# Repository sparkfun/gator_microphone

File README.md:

SparkFun gator:microphone - micro:bit Accessory Board 
=============================

[*SparkFun gator:microphone - micro:bit Accessory Board (SEN-15289)*](https://www.sparkfun.com/products/15289)  

(Modify Description)
Electret microphone with multiple outputs.

* First output is the actual audio
* Second output is the amplitude envelope
* Third output is a binary "sound present" indication - high while sound is present, low otherwise.

Design and firmware files for the [VKey Voltage Keypad](https://www.sparkfun.com/products/12080).

Repository Contents
-------------------

* **/Hardware** - Eagle design files (.brd, .sch)
* **/Production** - Production panel files (.brd)

Documentation
--------------

* **[Hookup Guide](https://learn.sparkfun.com/tutorials/sparkfun-gatormicrophone-hookup-guide)** - Basic hookup guide for the gator:microphone.
* **[gator:microphone PXT Package](https://github.com/sparkfun/pxt-gator-microphone)** - PXT- package for the MakeCode gator:microphone extension.

License Information
-------------------

This product is _**open source**_! 

Please review the LICENSE.md file for license information. 

If you have any questions or concerns on licensing, please visit the [SparkFun Forum](https://forum.sparkfun.com/index.php) and post a topic. For more general questions related to our gator boards, please visit this section of the forum: [SparkFun Forums: Educational Products](https://forum.sparkfun.com/viewforum.php?f=155)

Distributed as-is; no warranty is given.

- Your friends at SparkFun.

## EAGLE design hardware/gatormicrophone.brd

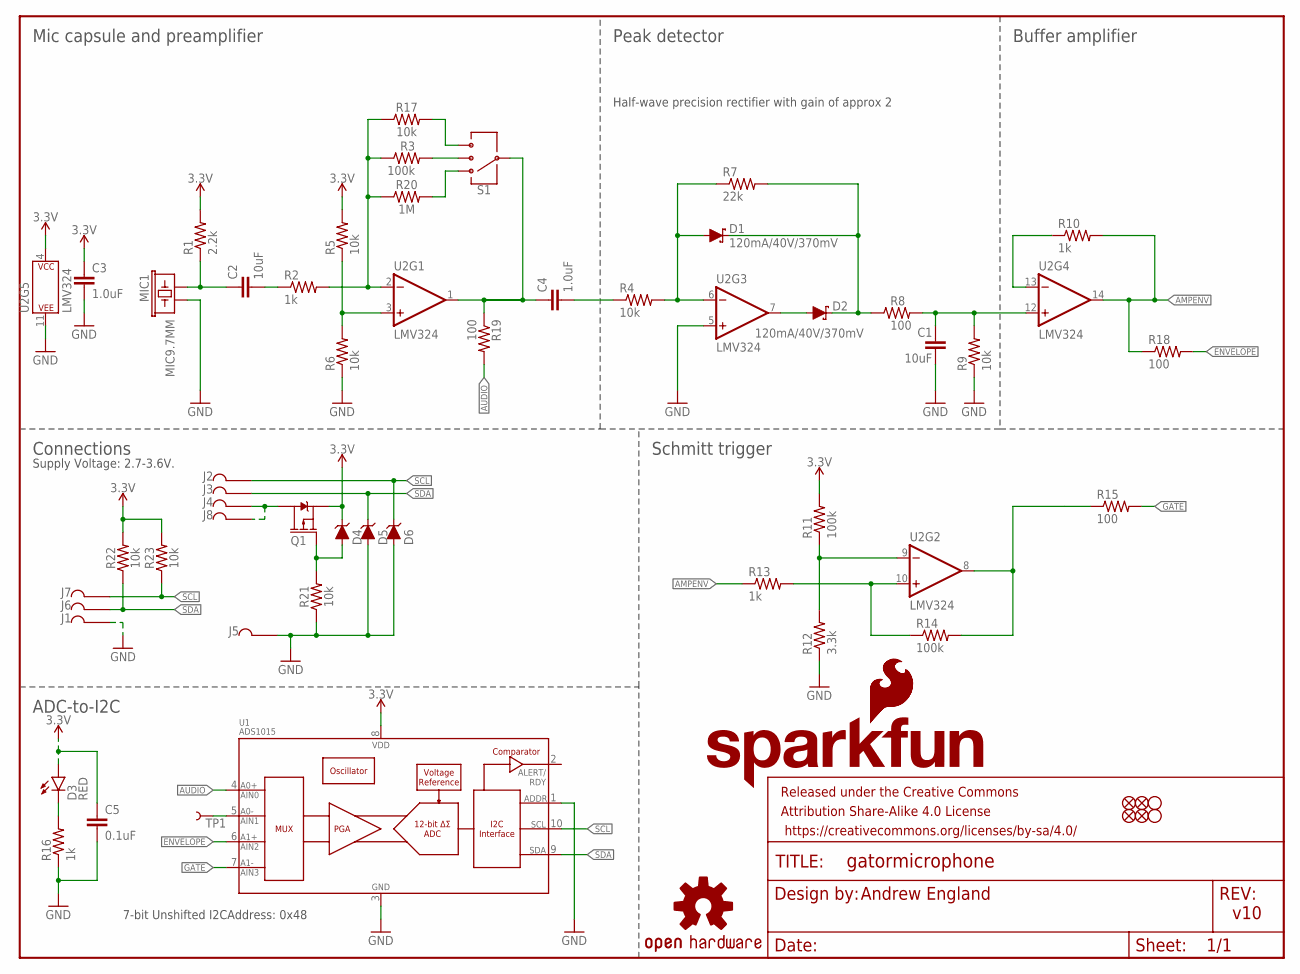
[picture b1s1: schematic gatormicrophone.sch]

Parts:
C1, C2: 10uF; 1206@1
C3, C4: 1.0uF; 0603
C5: 0.1uF; 0603
D1, D2: 120mA/40V/370mV; SOD-523
D3: RED; LED-0603
D4, D5, D6: 3.6V; SOD-323
FID1, FID2, FID3, FID4: FIDUCIAL1X2; FIDUCIAL-1X2
FRAME1: FRAME-LETTER; CREATIVE_COMMONS
H1, H2: STAND-OFFTIGHT; STAND-OFF-TIGHT
J1, J2, J3, J4, J5, J6, J7, J8: GATORGATOR_MINI; GATOR_MINI
LOGO1: OSHW-LOGOS; OSHW-LOGO-S
LOGO2: SFE_LOGO_NAME_FLAME.2_INCH; SFE_LOGO_NAME_FLAME_.2
LOGO3: SFE_LOGO_FLAME.2_INCH; SFE_LOGO_FLAME_.2
MIC1: MIC9.7MM; MIC-9.7MM
Q1: 2.5A/30V/105mΩ; SOT23-3
R1: 2.2k; 0603
R2, R10, R13, R16: 1k; 0603
R3, R11, R14: 100k; 0603
R4, R5, R6, R9, R17, R21, R22, R23: 10k; 0603
R7: 22k; 0603
R8, R15, R18, R19: 100; 0603
R12: 3.3k; 0603
R20: 1M; 0603
S1: SWITCH-SP3T-SMD; SWITCH_SP3T_SMD
TP1: TEST-POINT3; PAD.03X.03
U1: ADS1015; MSOP10
U2: LMV324; SO14

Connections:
3.3V: C3.1, C5.1, D3.A, D4.C, Q1.2 (S), R1.2, R5.2, R11.2, R22.2, R23.2, U1.8 (VDD), U2.4 (P$V+)
AMPENV: R10.2, R13.1, R18.1, U2.14 (OUT)
AUDIO: R19.2, U1.4 (AIN0)
ENVELOPE: R18.2, U1.6 (AIN2)
GATE: R15.2, U1.7 (AIN3)
GND: C1.2, C3.2, C5.2, D5.A, D6.A, J1.P$2, J5.P$2, MIC1.2, R6.1, R9.1, R12.1, R16.1, R21.1, U1.1 (ADDR), U1.3 (VSS), U2.5 (+IN), U2.11 (P$V-)
N$: C4.1, R19.1, S1.3, U2.1 (OUT)
unnamed: C2.1, MIC1.1, R1.1
unnamed: R5.1, R6.2, U2.3 (+IN)
unnamed: D3.C, R16.2
unnamed: R2.2, R3.1, R17.1, R20.1, U2.2 (-IN)
unnamed: C2.2, R2.1
unnamed: C4.2, R4.1
unnamed: D1.A, R4.2, R7.1, U2.6 (-IN)
unnamed: D2.A, U2.7 (OUT)
unnamed: D1.C, D2.C, R7.2, R8.1
unnamed: C1.1, R8.2, R9.2, U2.12 (+IN)
unnamed: R10.1, U2.13 (-IN)
unnamed: TP1.P$1, U1.5 (AIN1)
unnamed: R17.2, S1.4
unnamed: R3.2, S1.2
unnamed: R11.1, R12.2, U2.9 (-IN)
unnamed: R13.2, R14.1, U2.10 (+IN)
unnamed: R14.2, R15.1, U2.8 (OUT)
unnamed: R20.2, S1.1
unnamed: J4.P$2, J8.P$2, Q1.3 (D)
unnamed: D4.A, Q1.1 (G), R21.2
SCL: D6.C, J2.P$2, J7.P$2, R23.1, U1.10 (SCL)
SDA: D5.C, J3.P$2, J6.P$2, R22.1, U1.9 (SDA)

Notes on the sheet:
Andrew England
v10
Mic capsule and preamplifier
Peak detector
Buffer amplifier
Connections
Schmitt trigger
Half-wave precision rectifier with gain of approx 2
Supply Voltage: 2.7-3.6V.
ADC-to-I2C
7-bit Unshifted I2CAddress: 0x48

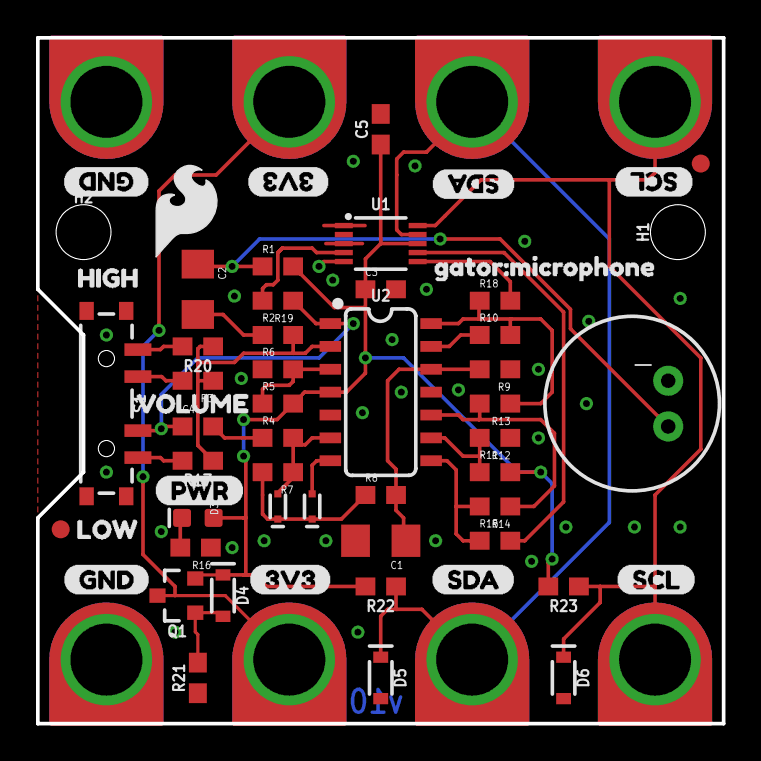
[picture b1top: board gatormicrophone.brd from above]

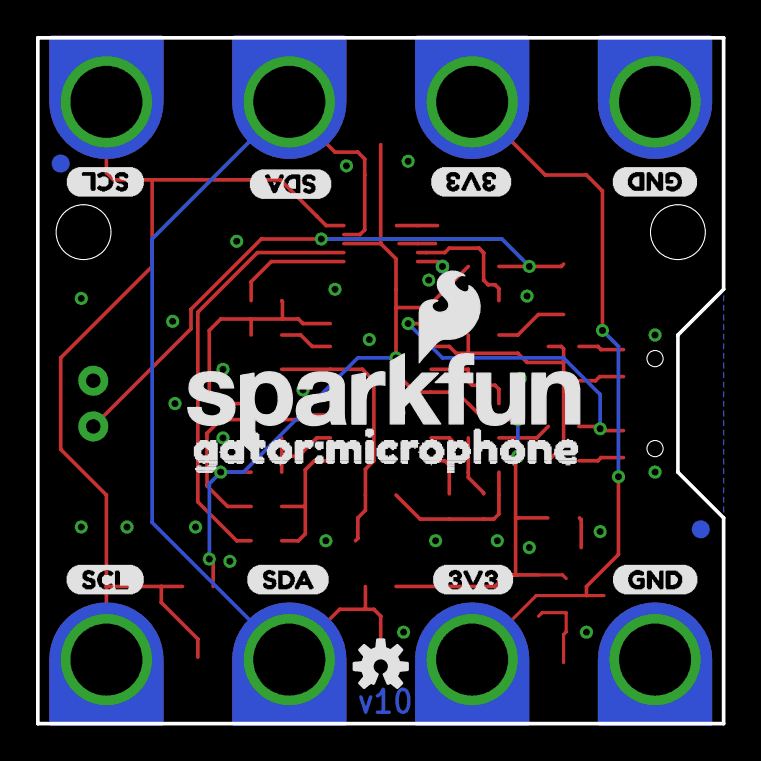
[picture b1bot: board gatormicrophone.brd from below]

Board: 2 copper layers, 38.1 x 38.1 mm, 81 parts (14 on the bottom side), 29 nets.

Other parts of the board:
U$1, U$7, U$11, U$18: 3V31
U$2, U$9, U$13, U$20: SCL1
U$3, U$8, U$12, U$19: SDA2
U$4: PWR0
U$5, U$6, U$10, U$17: GND0
U$14: GATOR#MICROPHONE1
U$15: LOW1
U$16: VOLUME2
U$21: HIGH0
U$22: ORDERING_INSTRUCTIONS
U$24: GATOR#MICROPHONE0

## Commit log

2019-02-27 initial layout
2019-02-28 adding protection circuitry
2019-03-18 post engineer run of checklist
2019-03-18 adding to measures layer
2019-04-16 pre design review changes
2019-04-19 engineer run of checklist
2019-04-22 panel
2019-04-22 adding panel
2019-06-12 Update to current product information
    Will need to update forum link and description
2019-06-12 Add license
2019-06-12 Update
    Troubleshooting link and product description
2019-06-14 cleaning repo
2021-12-06 Remove old panel files

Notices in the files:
parts and their libraries:
SparkFun-Aesthetics: Licensing: CC v3.0 Share-Alike You are welcome to use this library for commercial purposes.
SparkFun-Aesthetics: Released under the Creative Commons Attribution Share-Alike 4.0 License
SparkFun-Aesthetics: https://creativecommons.org/licenses/by-sa/4.0
